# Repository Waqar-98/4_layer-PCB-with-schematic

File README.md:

4-Layer ESP32 Sensor Board

A battery-powered, USB-C rechargeable ESP32-C3 sensor node integrating environmental (temperature/humidity/pressure), ambient light, and sound sensing, with onboard USB-to-UART programming, microSD data logging, and an I2C display header. This repository is a **revision** of the original 2-layer design, re-laid-out as a **4-layer PCB** (dedicated inner power/ground planes) for improved signal integrity and routing.

| | |
|---|---|
| **MCU/Module** | ESP32-C3-WROOM-02-H4 (U3) |
| **USB-UART Bridge** | Silicon Labs CP2102N-A02-GQFN20 (U4) |
| **Layers** | 4 (F.Cu, In1.Cu, In2.Cu, B.Cu) |
| **Interfaces** | USB-C (USB 2.0), I2C, microSD (SPI), SPI NOR flash, GPIO breakout |
| **Power** | USB-C 5 V input, single-cell LiPo (JST 2 mm), onboard charge management |
| **Revision** | 2 (4-layer revision) |
| **Status** | In development |

---

## Table of Contents

1. [Overview](#1-overview)
2. [Features](#2-features)
3. [Hardware Description](#3-hardware-description)
4. [Schematics](#4-schematics)
5. [PCB Layout](#5-pcb-layout)
6. [ESP32-C3 Pin Mapping](#6-esp32-c3-pin-mapping)
7. [Connector Pinout](#7-connector-pinout)
8. [Power Supply](#8-power-supply)
9. [Getting Started](#9-getting-started)
10. [Repository Structure](#10-repository-structure)
11. [Bill of Materials](#11-bill-of-materials)
12. [Revision History](#12-revision-history)

---

## 1. Overview

This board is a compact, self-contained sensor node built around the ESP32-C3-WROOM-02-H4 module. It integrates a BME280 environmental sensor, a TEMT6000 ambient light sensor, and an electret microphone with an adjustable-gain amplifier, alongside a microSD card slot and an external SPI NOR flash for local data logging. Power comes from either USB-C or a single-cell LiPo battery, with onboard charge management and power-path switching so the board can run and charge simultaneously. An onboard CP2102N provides USB-to-UART programming and an automatic reset/bootloader-entry circuit, so no external programmer is required.

This revision re-lays out the board on **4 copper layers** instead of 2, adding dedicated inner power (3.3 V) and ground planes. This improves return-path continuity and reduces plane impedance/noise for the analog sensor front-ends (microphone amplifier, light sensor) and the SPI/I2C digital buses, compared with the original 2-layer version.

## 2. Features

- **ESP32-C3-WROOM-02-H4** (U3) — RISC-V single-core Wi-Fi/BLE module
- **BME280** (U7) environmental sensor — temperature, humidity, and pressure over I2C, address-select pad for 0x76/0x77
- **TEMT6000X01** (Q1) ambient light phototransistor with RC-filtered analog output
- **Electret microphone** (MK1, CMC-5042PF-AC) with a **MAX4466EXK+T** (U8) op-amp amplifier and a trimmer potentiometer (R17, 100 kΩ) for adjustable gain
- **microSD card slot** (J3, GSD090012SEU) on a shared SPI bus
- **32 Mbit external SPI NOR flash** (U6, W25Q32JVSSIQ) sharing the same SPI bus with an independent chip select, for onboard data logging separate from the module's program flash
- **Onboard USB-to-UART bridge** (U4, CP2102N-A02-GQFN20) with USB ESD protection (U5, USBLC6-2SC6) — no external FTDI/CH340 adapter needed to program the board
- **Automatic reset/bootloader-entry circuit** using two BC817 transistors (Q2, Q3) driven from DTR/RTS, following the standard ESP32 auto-program sequence
- **USB-C power input** (J1) with 5.1 kΩ CC pull-downs for default 5 V/USB 2.0 negotiation
- **LiPo charge management** via a **MCP73871** charger IC (U1) with power-path management, tri-color charge-status LEDs (charging/charged/power-good), and battery connector (J2, JST 2 mm)
- **LM1117MPX-3.3** LDO (U2) regulates the system 3.3 V rail
- Manual **BOOT** and **RESET** buttons (SW1, SW2) in addition to the automatic DTR/RTS circuit
- I2C header (J4) for an external OLED display
- 5-pin breakout header (J6) exposing 3.3 V, GND, and three spare GPIOs (GPIO8, GPIO18, GPIO19)
- Five test points (TP1–TP5) on the shared SPI bus (MOSI, MISO, SCLK, CS_SD, CS) for debugging
- **4-layer stack-up** with dedicated inner 3.3 V and GND planes (this revision)

## 3. Hardware Description

**Power input and charging.** USB-C VBUS (J1) passes through a resettable fuse (F1) to the `+5V_USB` rail. This rail feeds a MCP73871 LiPo charger IC (U1) configured with power-path management: it charges a single-cell LiPo connected at J2 while simultaneously supplying the system load from its `OUT` pin, so the board can operate while charging. Three status outputs (`STAT1`, `STAT2`, `PG`) drive a red/green/blue LED trio (D1–D3) through 470 Ω resistors, giving a visual charge/power-good indication. `OUT` feeds through a ferrite bead (FB1) into an LM1117MPX-3.3 LDO (U2), which produces the board's 3.3 V rail used by every other block.

**MCU and USB programming.** The ESP32-C3-WROOM-02-H4 (U3) is the central module. A CP2102N-A02-GQFN20 USB-to-UART bridge (U4), protected by a USBLC6-2SC6 ESD array (U5) on the USB data lines, connects the module's TX/RX to the host PC and exposes green/red (D5/D6) activity LEDs on its GPIO.2/GPIO.3 lines. DTR and RTS from the CP2102N drive two BC817 transistors (Q2, Q3) that implement the standard auto-reset/auto-bootloader circuit on the `EN` and `BOOT` (GPIO9) lines, so the board can be flashed without manually holding a button. Manual BOOT (SW1) and RESET (SW2) buttons are also provided, each with an RC debounce network.

Notably, because the ESP32-C3's boot-mode strapping pin is GPIO9 (unlike the original ESP32, which straps on GPIO0), this design routes GPIO9 to the `BOOT` net for auto-programming and frees GPIO0 for use as an analog input for the microphone signal (`MIC_OUT`).

**Storage.** A microSD socket (J3, GSD090012SEU) and a 32 Mbit SPI NOR flash (U6, W25Q32JVSSIQ) share one SPI bus (`MOSI_DI`, `MISO_DO`, `SCLK`) with independent chip-select lines (`CS_SD`, `CS`). Series resistors (R15, R20, R22 — annotated on the schematic as ~50 Ω) sit on the shared bus lines to damp ringing at high SPI clock rates. Five test points (TP1–TP5) break out the same bus for probing.

**Sensors.** A BME280 (U7) provides temperature, humidity, and pressure over I2C, with SDA/SCL pull-ups (R24, R25) and a pad to select the I2C address by tying `SDO` to GND (0x76) or `VDDIO` (0x77) — this board ties it to GND. A TEMT6000X01 phototransistor (Q1) with a 10 kΩ pull-down (R23) and RC filtering forms a simple ambient-light sensor read as an analog voltage. An electret microphone (MK1) is biased and AC-coupled into a MAX4466EXK+T op-amp (U8) configured as a non-inverting amplifier; a 22 kΩ resistor plus a 100 kΩ trimmer potentiometer (R31, R17) in the feedback path set the gain, with a 100 pF capacitor (C20) rolling off high-frequency noise.

**User interface.** A 4-pin I2C header (J4, B4B-XH-AM) breaks out 3.3 V/SDA/SCL/GND for an external OLED display. A 5-pin header (J6) exposes 3.3 V, GND, and the three GPIOs (GPIO8/18/19) not otherwise used by the design.

**Stack-up (this revision).** The board was re-laid-out from 2 to 4 copper layers: `F.Cu` (top signal), `In1.Cu` (inner plane), `In2.Cu` (inner plane), `B.Cu` (bottom signal). The inner layers are used as continuous 3.3 V and GND planes, giving the top/bottom signal layers a solid adjacent reference plane and shortening high-frequency return paths for the SPI bus and analog front-ends.

## 4. Schematics

**Power and battery management** (root sheet — USB-C input, LiPo charger, LDO regulator, power-indicator LED, battery connector)

**ESP32-C3-02 and USB-to-UART converter** (MCU, CP2102N USB bridge, SPI flash, microSD module, test points)

**Sensors** (BME280, TEMT6000 light sensor, electret microphone and amplifier)

**User interface** (OLED I2C header, GPIO breakout header, reset/boot buttons, auto-program circuit)

## 5. PCB Layout

Four-layer board (top copper in red, bottom copper in blue, inner planes not separately colored in the 2D view) with a stepped outline: the sensor cluster (microphone, light sensor, BME280) sits along the top edge, charging/regulation/USB circuitry occupies the left and lower-left, and the ESP32 module, SPI flash, and microSD slot are grouped on the right where the board extends further along the top edge. A hatched keep-out zone sits directly next to the ESP32-C3-WROOM-02 footprint, consistent with the module's onboard PCB antenna clearance requirement. A second hatched/unpopulated zone, silkscreened `proto#2`, appears to be a reserved prototyping area. The layout includes multiple mounting holes and five silkscreened test points (TP1–TP5) on the shared SPI bus — exact hole counts, diameters, and keep-out dimensions should be confirmed against the PCB source file.

**3D Render**

## 6. ESP32-C3 Pin Mapping

Pin assignments below are read directly from the ESP32-C3-WROOM-02-H4 (U3) schematic symbol. Verify against the source design files prior to firmware development.

| Module Pin | GPIO | Net / Function |
|---|---|---|
| 1 | 3V3 | 3.3 V supply |
| 2 | EN | Chip enable / reset (auto-program + RESET button) |
| 18 | IO0 | `MIC_OUT` — microphone amplifier analog output |
| 17 | IO1 | `PHOTO_C` — light sensor analog output |
| 16 | IO2 | `MISO_DO` — shared SPI bus (flash + microSD) |
| 15 | IO3 | `SCL` — I2C clock (BME280, OLED header) |
| 3 | IO4 | `SDA` — I2C data (BME280, OLED header) |
| 4 | IO5 | `CS_SD` — microSD chip select |
| 5 | IO6 | `SCLK` — shared SPI bus clock (via R20) |
| 6 | IO7 | `MOSI_DI` — shared SPI bus data out (via R15) |
| 7 | IO8 | `GPIO8` — broken out to J6 |
| 8 | IO9 | `BOOT` — boot-mode strap / auto-program (via Q3) |
| 10 | IO10 | `CS` — SPI flash chip select |
| 13 | IO18 | `GPIO18` — broken out to J6 |
| 14 | IO19 | `GPIO19` — broken out to J6 |
| 12 | TXD | `RX_TX` — to CP2102N |
| 11 | RXD | `TX_RX` — from CP2102N |
| — | GND | Ground |

## 7. Connector Pinout

Pin assignments below are derived from the schematics. Verify against the source design files and PCB silkscreen prior to integration.

**J1 — USB-C Receptacle (USB 2.0 only)**

Standard USB-C receptacle; only the VBUS, GND, D+/D− and CC1/CC2 pins are used (SBU1/SBU2 and the SuperSpeed pairs are unconnected). CC1 and CC2 each carry a 5.1 kΩ pull-down (R4, R3) to present the board as a default-power USB 2.0 sink.

**J2 — Battery Connector (JST_2mm_LiPo)**

| Pin | Signal |
|-----|--------|
| 1 | VBAT (+) |
| 2 | GND |

**J3 — microSD Socket (GSD090012SEU), SPI mode**

| Pin | Signal |
|-----|--------|
| 4 | VDD1 (3.3 V) |
| 2 | CMD ← `MOSI_DI` |
| 5 | CLK ← `SCLK` |
| 7 | DAT0 → `MISO_DO` (pull-up R16) |
| 8 | DAT1 (not used in SPI mode) |
| 9 | DAT2 |
| 1 | CD/DAT3 → `CS_SD` (pull-up R19, 10 kΩ) |
| — | CD_IND, WP (not populated) |
| 3, 6 | VSS1/VSS2 (GND) |
| GS | SHIELD_GND |

**J4 — OLED Display Connector, I2C (B4B-XH-AM, 4-pin)**

| Pin | Signal |
|-----|--------|
| 1 | 3.3 V |
| 2 | SDA |
| 3 | SCL |
| 4 | GND |

**J6 — Spare GPIO Breakout (Conn_01x05, 5-pin)**

| Pin | Signal |
|-----|--------|
| 1 | 3.3 V |
| 2 | GPIO8 |
| 3 | GPIO18 |
| 4 | GPIO19 |
| 5 | GND |

**TP1–TP5 — Test Points**

| Test Point | Net |
|---|---|
| TP1 | MOSI_DI |
| TP2 | MISO_DO |
| TP3 | SCLK |
| TP4 | CS_SD |
| TP5 | CS |

## 8. Power Supply

| Parameter | Value |
|---|---|
| Input | USB-C 5 V (VBUS, via resettable fuse F1) or single-cell LiPo (J2) |
| Charger IC | MCP73871 (U1) — LiPo charger with power-path management |
| Regulator | LM1117MPX-3.3/NDPB (U2), LDO |
| System rail | 3.3 V |
| Charge status indication | Tri-color LED (D1 red / D2 green / D3 blue) driven from STAT2, STAT1/LBO, PG |
| Power-good indicator | Red LED (D4) on the 3.3 V rail via R10 (330 Ω) |
| Input filtering | C1 (0.1 µF) on VBUS; C2/C3 (0.1 µF/10 µF) on LDO input; C4/C5 (10 µF/0.1 µF) on LDO output; C6 (1 µF) on charger IN |

## 9. Getting Started

1. **Power:** Connect a USB-C cable to J1 for bench power/programming, and/or connect a single-cell LiPo battery to J2 for portable operation. The board can run while charging.
2. **Programming:** Connect the board to a host PC via USB-C. The onboard CP2102N enumerates as a serial port; the DTR/RTS auto-program circuit puts the ESP32-C3 into bootloader mode automatically when flashing (e.g. via `esptool.py` or the Arduino/PlatformIO/ESP-IDF toolchains). Use the BOOT (SW1) and RESET (SW2) buttons manually if auto-programming is disabled or unresponsive.
3. **Serial/communication:** The BME280 and any OLED display connected at J4 share the I2C bus on GPIO3 (SCL) / GPIO4 (SDA). The microSD card and external SPI flash share one SPI bus (GPIO6/7/2) with independent chip selects on GPIO5 (`CS_SD`) and GPIO10 (`CS`).
4. **Opening the design:** Open `hardware/kicad/ESP32 sensor board.kicad_pro` in KiCad 8/9+ to view or edit the schematic and 4-layer PCB layout.
5. **Fabrication:** Fabrication-ready Gerbers and drill files for the current 4-layer revision are in `hardware/gerbers/`, generated directly from the KiCad PCB source.

## 10. Repository Structure

```
.
├── docs/
│   └── images/
│       ├── schematic-power-management.png
│       ├── schematic-mcu-usb-uart.png
│       ├── schematic-sensors.png
│       ├── schematic-user-interface.png
│       ├── pcb-layout.png
│       └── pcb-3d-render.png
├── hardware/
│   ├── kicad/            # Full KiCad 4-layer project source (schematics, PCB, libraries, datasheets)
│   ├── gerbers/           # Fabrication-ready Gerber and drill files (4-layer)
│   └── bom.csv            # Bill of materials, exported from the schematic
└── README.md
```

## 11. Bill of Materials

A full bill of materials, generated from the schematic, is available at [`hardware/bom.csv`](hardware/bom.csv). Key components:

| Reference | Component | Description |
|---|---|---|
| U1 | MCP73871 | LiPo charger IC with power-path management |
| U2 | LM1117MPX-3.3/NDPB | 3.3 V LDO regulator |
| U3 | ESP32-C3-WROOM-02-H4 | Wi-Fi/BLE MCU module |
| U4 | CP2102N-A02-GQFN20 | USB-to-UART bridge |
| U5 | USBLC6-2SC6 | USB D+/D− ESD protection array |
| U6 | W25Q32JVSSIQ | 32 Mbit SPI NOR flash |
| U7 | BME280 | Environmental sensor (temperature/humidity/pressure) |
| U8 | MAX4466EXK+T | Microphone amplifier op-amp |
| Q1 | TEMT6000X01 | Ambient light phototransistor |
| Q2, Q3 | BC817 | NPN transistors, auto-reset/bootloader circuit |
| MK1 | CMC-5042PF-AC | Electret microphone |
| J1 | USB_C_Receptacle | USB-C connector |
| J2 | JST_2mm_LiPo | Battery connector |
| J3 | GSD090012SEU | microSD card socket |
| J4 | B4B-XH-AM | 4-pin JST-XH, OLED I2C connector |
| J6 | Conn_01x05 | 5-pin GPIO breakout header |
| SW1, SW2 | Tactile switch | BOOT and RESET buttons |
| D1–D3 | LED (RGB, discrete) | Charge status indicator |
| D4 | LED (red) | Power-good indicator |
| D5, D6 | LED (green/red) | USB activity indicators |
| F1 | Resettable fuse | VBUS overcurrent protection |
| FB1 | Ferrite bead | Charger output filtering |

## 12. Revision History

| Revision | Date | Notes |
|---|---|---|
| 1 | 2026-06-29 | Initial 2-layer design |
| 2 | 2026-09-09 | Revised to 4-layer stack-up with dedicated inner power/ground planes; gerbers and BOM regenerated for the new layout |

---

**Author:** Waqar-98

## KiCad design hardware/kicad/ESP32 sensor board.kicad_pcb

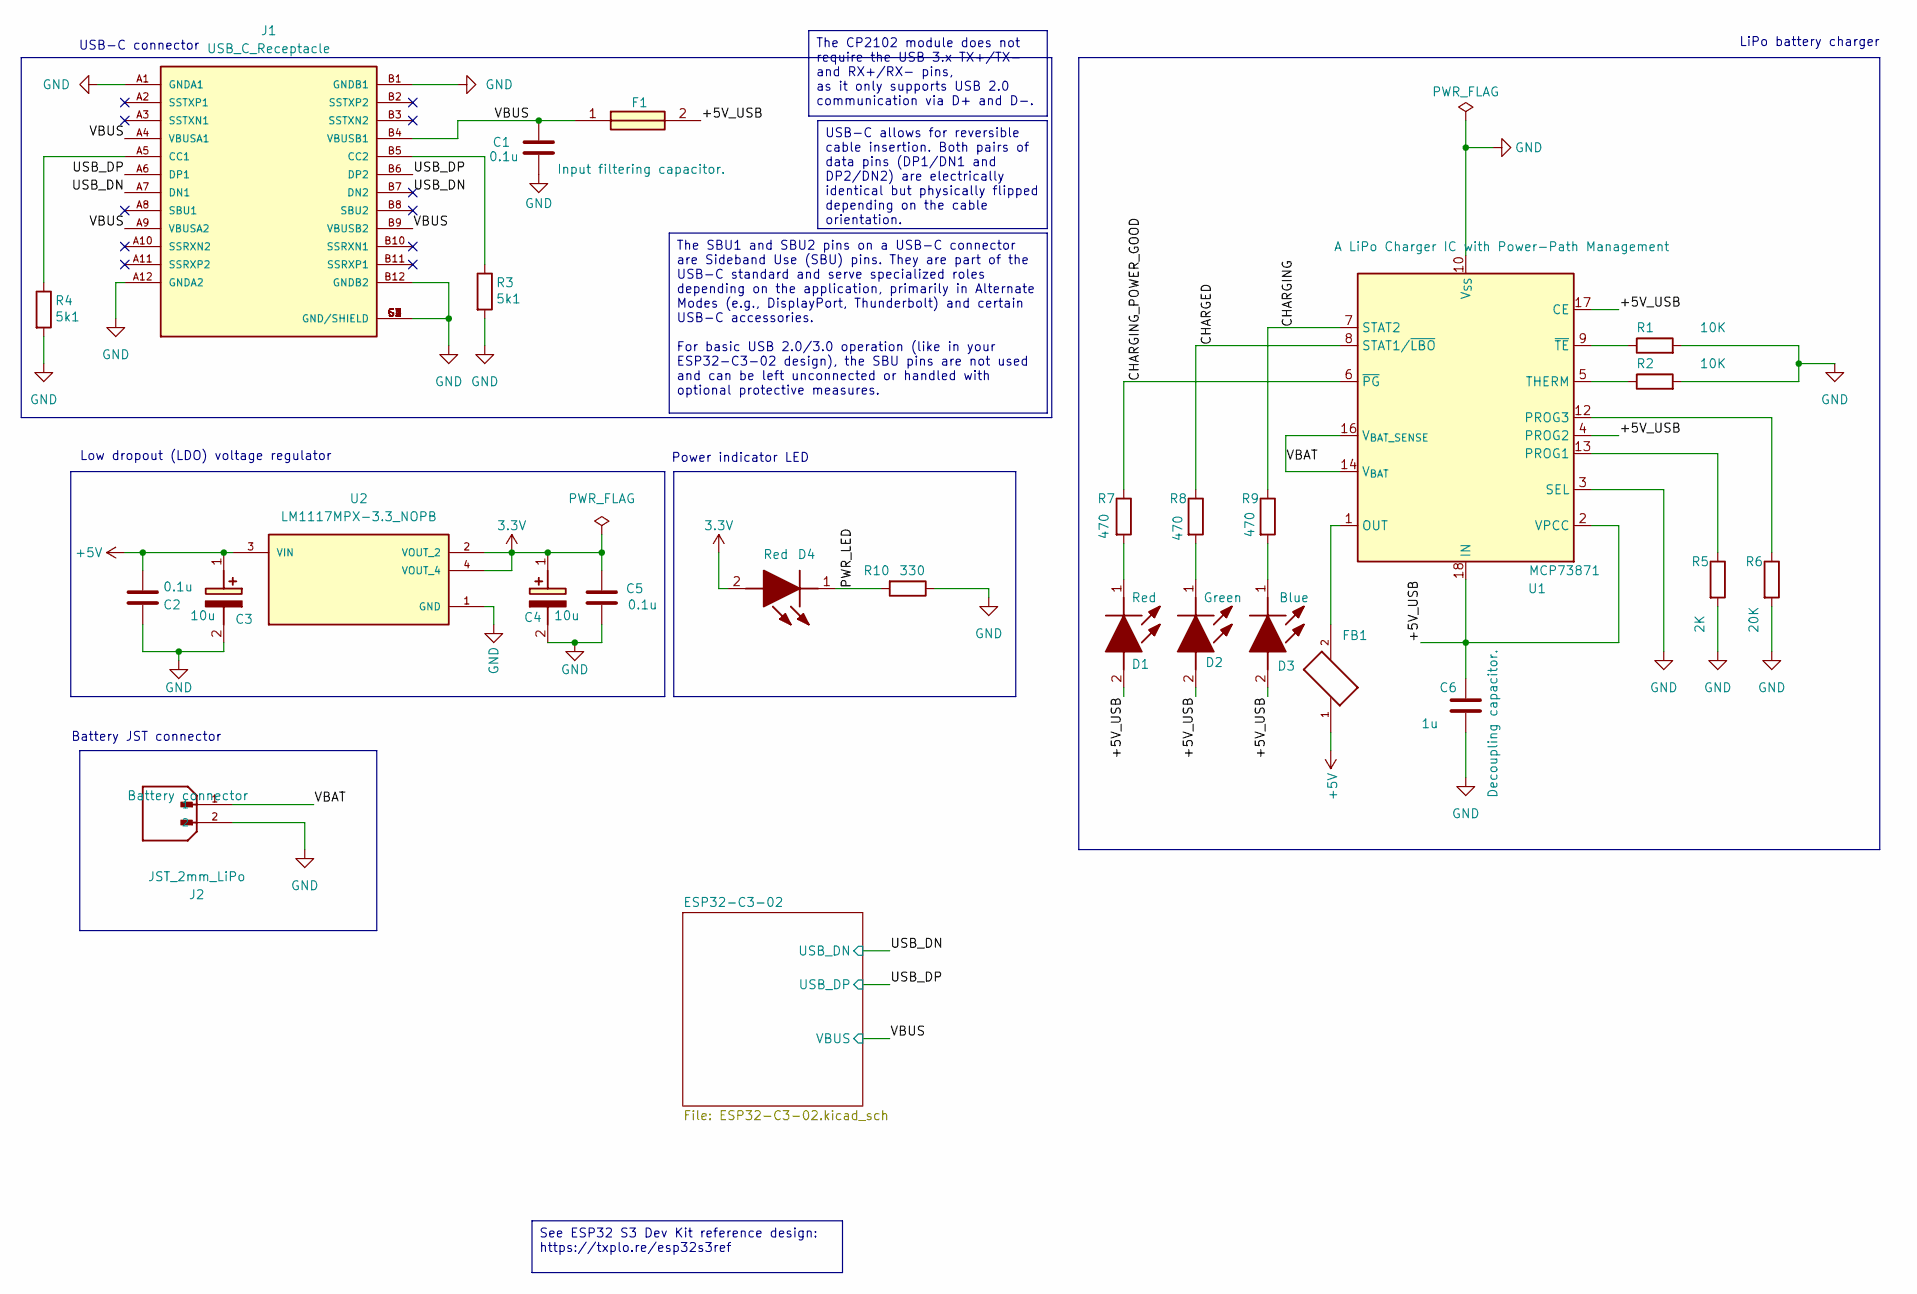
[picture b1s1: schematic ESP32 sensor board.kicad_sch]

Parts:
C1, C2, C5: 0.1u; C_0805_2012Metric; Voltage 1kV; Tolerance 100%
C3, C4: 10u; T491A; Voltage 1kV; Tolerance 100%; Manufacturer_Part_Number T491A106K010AT7280; Mouser Part Number 80-T491A106K107280
C6: 1u; C_0805_2012Metric; Voltage 1kV; Tolerance 100%
D1, D4: Red; LEDC2012X120N; Manufacturer_Part_Number LTST-C170KRKT; Mouser Part Number 859-LTST-C170KRKT
D2: Green; LEDC2012X120N; Manufacturer_Part_Number LTST-C170GKT; Mouser Part Number 859-LTST-C170GKT
D3: Blue; LEDC2012X120N; Manufacturer_Part_Number LTST-C170TBKT; Mouser Part Number 859-LTST-C170TBKT
F1: 0ZCH0110AF2E; FUSC3226X100N; Manufacturer_Part_Number 0ZCH0110AF2E
FB1: FBMJ2125HM330-T; BEADC2012X105N
J1: USB_C_Receptacle; BELFUSE_SS-52400-002; PARTREV A0
J2: JST_2mm_LiPo; JST_B2B-PH-SM4-TB; Manufacturer_Part_Number ?
R1, R2: 10K; R_0805_2012Metric
R3, R4: 5k1; R_0805_2012Metric
R5: 2K; R_0805_2012Metric
R6: 20K; R_0805_2012Metric
R7, R8, R9: 470; R_0805_2012Metric
R10: 330; R_0805_2012Metric
U1: MCP73871; QFN-20-1EP_4x4mm_P0.5mm_EP2.5x2.5mm; Manufacturer_Part_Number MCP73871-4CCI/ML
U2: LM1117MPX-3.3_NOPB; VREG_LM1117MPX-3.3; Mouser Part Number 926-LM1117MPX3.3NOPB

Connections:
3.3V: C4.1 (+), C5.1, D4.2 (A), U2.2 (VOUT_2), U2.4 (VOUT_4); also elsewhere on the board
+5V: C2.1, C3.1 (+), FB1.1, U2.3 (VIN)
/+5V_USB: C6.1, D1.2 (A), D2.2 (A), D3.2 (A), F1.2, U1.2 (VPCC), U1.4 (PROG2), U1.17 (CE), U1.18 (IN), U1.19 (IN)
/CHARGED: R8.1, U1.8 (STAT1/~LBO)
/CHARGING: R9.1, U1.7 (STAT2)
/CHARGING_POWER_GOOD: R7.1, U1.6 (~PG)
/PWR_LED: D4.1 (K), R10.2
/USB_DN: J1.A7 (DN1), J1.B7 (DN2); also elsewhere on the board
/USB_DP: J1.A6 (DP1), J1.B6 (DP2); also elsewhere on the board
/VBAT: J2.1, U1.14 (V_{BAT}), U1.15 (V_{BAT}), U1.16 (V_{BAT_SENSE})
/VBUS: C1.1, F1.1, J1.A4 (VBUSA1), J1.A9 (VBUSA2), J1.B4 (VBUSB1), J1.B9 (VBUSB2); also elsewhere on the board
unnamed: D1.1 (K), R7.2
unnamed: D2.1 (K), R8.2
unnamed: D3.1 (K), R9.2
unnamed: FB1.2, U1.1 (OUT), U1.20 (OUT)
unnamed: J1.A5 (CC1), R4.1
unnamed: J1.B5 (CC2), R3.1
unnamed: R5.1, U1.13 (PROG1)
unnamed: R6.1, U1.12 (PROG3)
unnamed: R2.1, U1.5 (THERM)
unnamed: R1.1, U1.9 (~TE)

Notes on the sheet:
USB-C connector
LiPo battery charger
Power indicator LED
Low dropout (LDO) voltage regulator
Battery JST connector
The CP2102 module does not require the USB 3.x TX+/TX- and RX+/RX- pins, as it only supports USB 2.0 communication via D+ and D-.
See ESP32 S3 Dev Kit reference design: https://txplo.re/esp32s3ref
The SBU1 and SBU2 pins on a USB-C connector are Sideband Use (SBU) pins. They are part of the USB-C standard and serve specialized roles depending on the application, primarily in Alternate Modes (e.g., DisplayPort, Thunderbolt) and certain USB-C accessories. For basic USB 2.0/3.0 operation (like i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
USB-C allows for reversible cable insertion. Both pairs of data pins (DP1/DN1 and DP2/DN2) are electrically identical but physically flipped depending on the cable orientation.

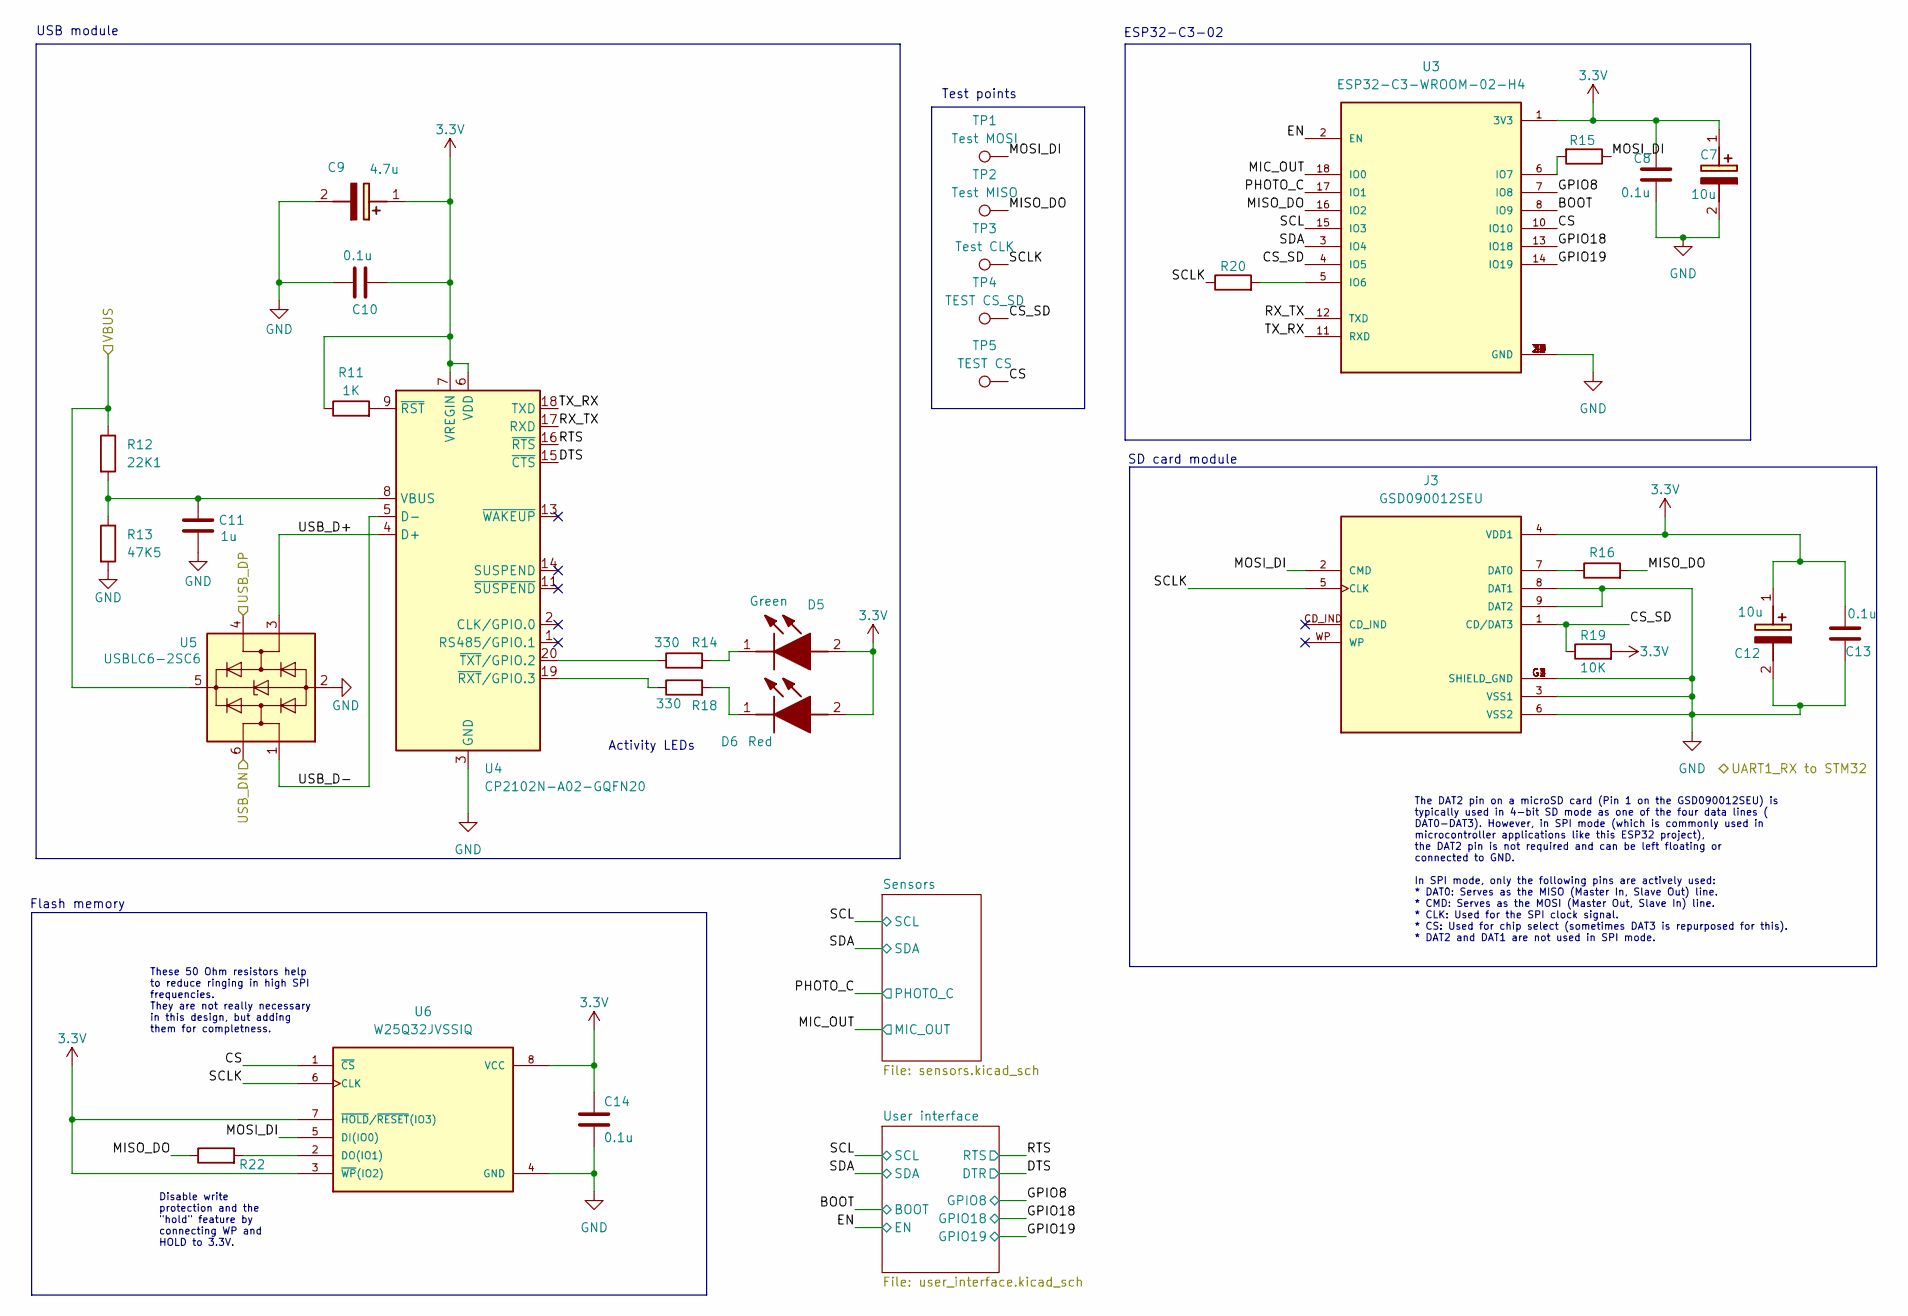
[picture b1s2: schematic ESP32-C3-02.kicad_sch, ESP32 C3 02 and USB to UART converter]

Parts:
C7, C12: 10u; T491A; Voltage 1kV; Tolerance 100%; Manufacturer_Part_Number T491A106K010AT7280; Mouser Part Number 80-T491A106K107280
C8, C10, C13, C14: 0.1u; C_0805_2012Metric; Voltage 1kV; Tolerance 100%
C9: 4.7u; T491A; Voltage 1kV; Tolerance 100%; Manufacturer_Part_Number T491A106K010AT7280; Mouser Part Number 80-T491A106K107280
C11: 1u; C_0805_2012Metric; Voltage 1kV; Tolerance 100%
D5: Green; LEDC2012X120N; Manufacturer_Part_Number LTST-C170GKT; Mouser Part Number 859-LTST-C170GKT
D6: Red; LEDC2012X120N; Manufacturer_Part_Number LTST-C170KRKT; Mouser Part Number 859-LTST-C170KRKT
J3: GSD090012SEU; AMPHENOL_GSD090012SEU; PARTREV E
R11: 1K; R_0805_2012Metric
R12: 22K1; R_0805_2012Metric
R13: 47K5; R_0805_2012Metric
R14, R18: 330; R_0805_2012Metric
R15, R16, R20, R22: 50; R_0805_2012Metric
R19: 10K; R_0805_2012Metric
TP1: Test MOSI; TestPoint_Pad_D1.0mm
TP2: Test MISO; TestPoint_Pad_D1.0mm
TP3: Test CLK; TestPoint_Pad_D1.0mm
TP4: TEST CS_SD; TestPoint_Pad_D1.0mm
TP5: TEST CS; TestPoint_Pad_D1.0mm
U3: ESP32-C3-WROOM-02-H4; MODULE_ESP32-C3-WROOM-02-H4; Manufacturer_Part_Number ESP32-C3-WROOM-02-H4
U4: CP2102N-A02-GQFN20; SiliconLabs_QFN-20-1EP_3x3mm_P0.5mm_EP1.8x1.8mm; Manufacturer_Part_Number CP2102N-A02-GQFN20
U5: USBLC6-2SC6; SOT-23-6; Manufacturer_Part_Number USBLC6-2SC6; Mouser Part Number 511-USBLC6-2SC6
U6: W25Q32JVSSIQ; SOIC127P790X216-8N; M_PART_NUMBER W25QXX

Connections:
3.3V: C7.1 (+), C8.1, C9.1 (+), C10.1, C12.1 (+), C13.2, C14.1, D5.2 (A), D6.2 (A), J3.4 (VDD1), R11.1, R19.2, U3.1 (3V3), U4.6 (VDD), U4.7 (VREGIN), U6.3 (~WP(IO2)), U6.7 (~HOLD/~RESET(IO3)), U6.8 (VCC); also elsewhere on the board
/ESP32-C3-02/CS: TP5.1, U3.10 (IO10), U6.1 (~CS)
/ESP32-C3-02/CS_SD: J3.1 (CD/DAT3), R19.1, TP4.1, U3.4 (IO5)
/ESP32-C3-02/DTS: U4.15 (~CTS); also elsewhere on the board
/ESP32-C3-02/GPIO8: U3.7 (IO8); also elsewhere on the board
/ESP32-C3-02/GPIO18: U3.13 (IO18); also elsewhere on the board
/ESP32-C3-02/GPIO19: U3.14 (IO19); also elsewhere on the board
/ESP32-C3-02/MIC_OUT: U3.18 (IO0); also elsewhere on the board
/ESP32-C3-02/MISO_DO: R16.2, R22.1, TP2.1, U3.16 (IO2)
/ESP32-C3-02/MOSI_DI: J3.2 (CMD), R15.1, TP1.1, U6.5 (DI(IO0))
/ESP32-C3-02/PHOTO_C: U3.17 (IO1); also elsewhere on the board
/ESP32-C3-02/RTS: U4.16 (~RTS); also elsewhere on the board
/ESP32-C3-02/RX_TX: U3.12 (TXD), U4.17 (RXD)
/ESP32-C3-02/SCL: U3.15 (IO3); also elsewhere on the board
/ESP32-C3-02/SCLK: J3.5 (CLK), R20.1, TP3.1, U6.6 (CLK)
/ESP32-C3-02/SDA: U3.3 (IO4); also elsewhere on the board
/ESP32-C3-02/TX_RX: U3.11 (RXD), U4.18 (TXD)
/ESP32-C3-02/USB_D+: U4.4 (D+), U5.3 (I/O2)
/ESP32-C3-02/USB_D-: U4.5 (D-), U5.1 (I/O1)
/USB_DN: U5.6 (I/O1); also elsewhere on the board
/USB_DP: U5.4 (I/O2); also elsewhere on the board
/VBUS: R12.1, U5.5 (VBUS); also elsewhere on the board
unnamed: D5.1 (K), R14.2
unnamed: D6.1 (K), R18.2
unnamed: J3.7 (DAT0), R16.1
unnamed: R20.2, U3.5 (IO6)
unnamed: R15.2, U3.6 (IO7)
unnamed: C11.1, R12.2, R13.1, U4.8 (VBUS)
unnamed: R11.2, U4.9 (~RST)
unnamed: R18.1, U4.19 (~RXT/GPIO.3)
unnamed: R14.1, U4.20 (~TXT/GPIO.2)
unnamed: R22.2, U6.2 (DO(IO1))

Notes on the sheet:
SD card module
Activity LEDs
Flash memory
USB module
Test points
ESP32-C3-02
Disable write protection and the "hold" feature by connecting WP and HOLD to 3.3V.
The DAT2 pin on a microSD card (Pin 1 on the GSD090012SEU) is typically used in 4-bit SD mode as one of the four data lines ( DAT0-DAT3). However, in SPI mode (which is commonly used in microcontroller applications like this ESP32 project), the DAT2 pin is not required and can be left floating or c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
These 50 Ohm resistors help to reduce ringing in high SPI frequencies. They are not really necessary in this design, but adding them for completness.

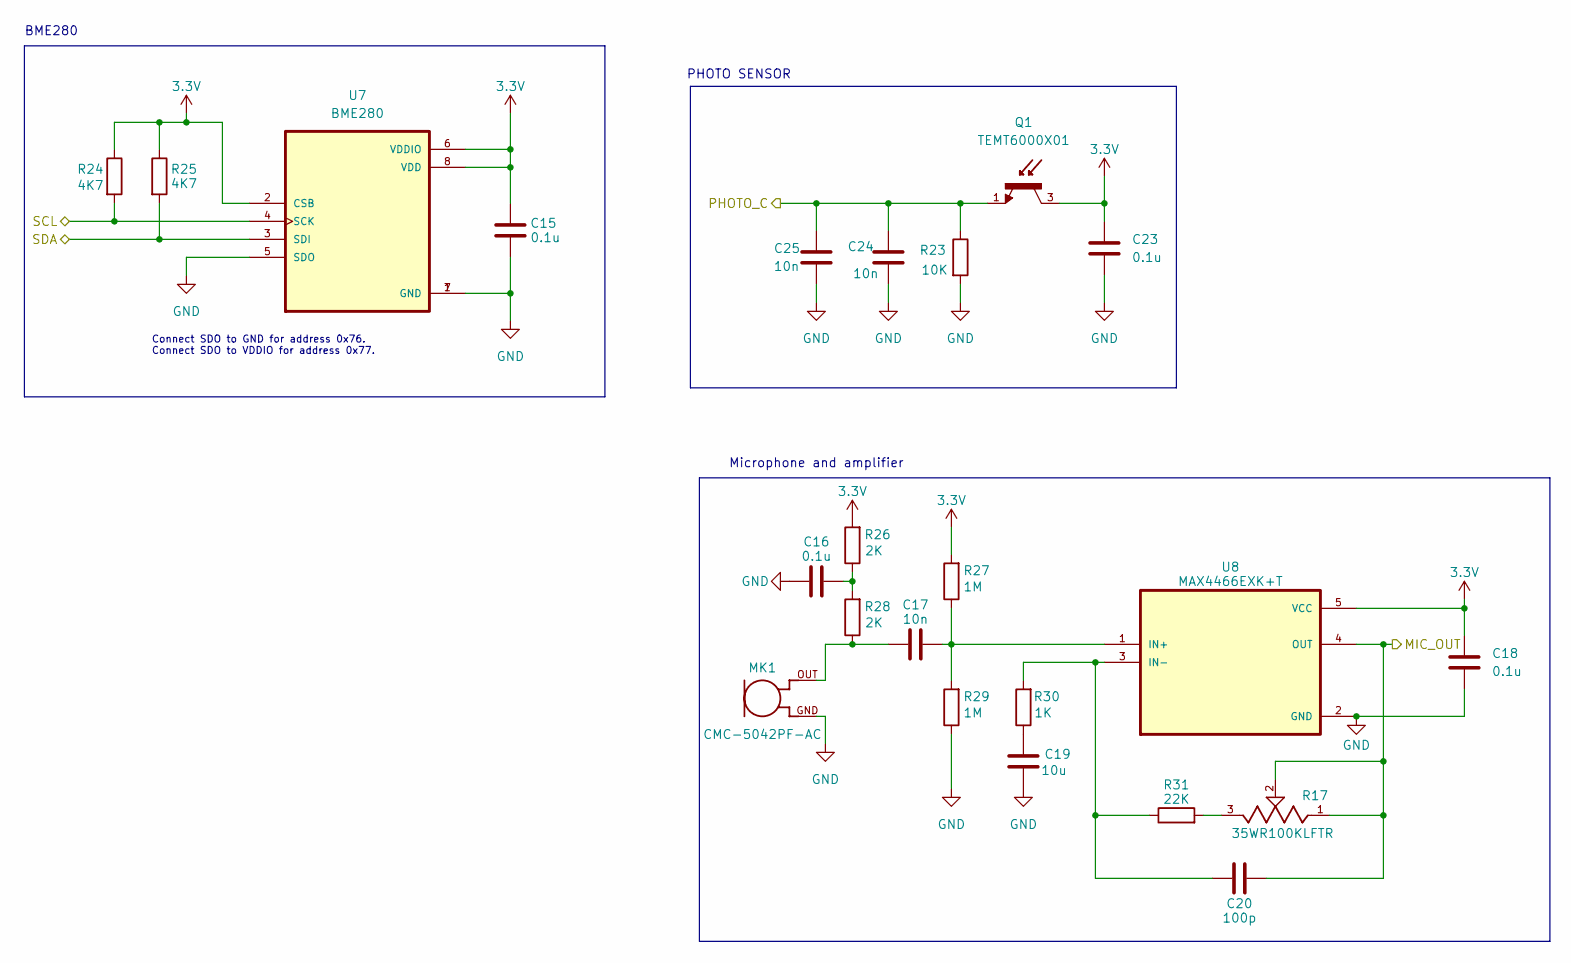
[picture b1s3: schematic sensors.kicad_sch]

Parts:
C15: 0.1u; C_0805_2012Metric; Voltage 1kV; Tolerance 100%
C16, C18, C23: 0.1u; C_0805_2012Metric
C17, C24, C25: 10n; C_0805_2012Metric
C19: 10u; C_0805_2012Metric
C20: 100p; C_0805_2012Metric
MK1: CMC-5042PF-AC; CUI_CMC-5042PF-AC; Manufacturer_Part_Number CMC-5042PF-AC
Q1: TEMT6000X01; TRANS_TEMT6000X01; PARTREV 1.9
R17: 35WR100KLFTR; TRIM_35WR100KLFTR; PARTREV D
R23: 10K; R_0805_2012Metric
R24, R25: 4K7; R_0805_2012Metric
R26, R28: 2K; R_0805_2012Metric
R27, R29: 1M; R_0805_2012Metric
R30: 1K; R_0805_2012Metric
R31: 22K; R_0805_2012Metric
U7: BME280; PSON65P250X250X100-8N; Manufacturer_Part_Number BME280
U8: MAX4466EXK+T; SOT65P210X110-5N; Manufacturer_Part_Number MAX4466EXK+T

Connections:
3.3V: C15.2, C18.1, C23.1, Q1.3, R24.1, R25.1, R26.2, R27.2, U7.2 (CSB), U7.6 (VDDIO), U7.8 (VDD), U8.5 (VCC); also elsewhere on the board
/ESP32-C3-02/MIC_OUT: C20.2, R17.1, R17.2, U8.4 (OUT); also elsewhere on the board
/ESP32-C3-02/PHOTO_C: C24.1, C25.1, Q1.1, R23.1; also elsewhere on the board
/ESP32-C3-02/SCL: R24.2, U7.4 (SCK); also elsewhere on the board
/ESP32-C3-02/SDA: R25.2, U7.3 (SDI); also elsewhere on the board
unnamed: C16.1, R26.1, R28.2
unnamed: C17.2, MK1.OUT, R28.1
unnamed: C19.2, R30.1
unnamed: R17.3, R31.2
unnamed: C17.1, R27.1, R29.2, U8.1 (IN+)
unnamed: C20.1, R30.2, R31.1, U8.3 (IN-)

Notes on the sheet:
PHOTO SENSOR
Microphone and amplifier
BME280
Connect SDO to GND for address 0x76. Connect SDO to VDDIO for address 0x77.

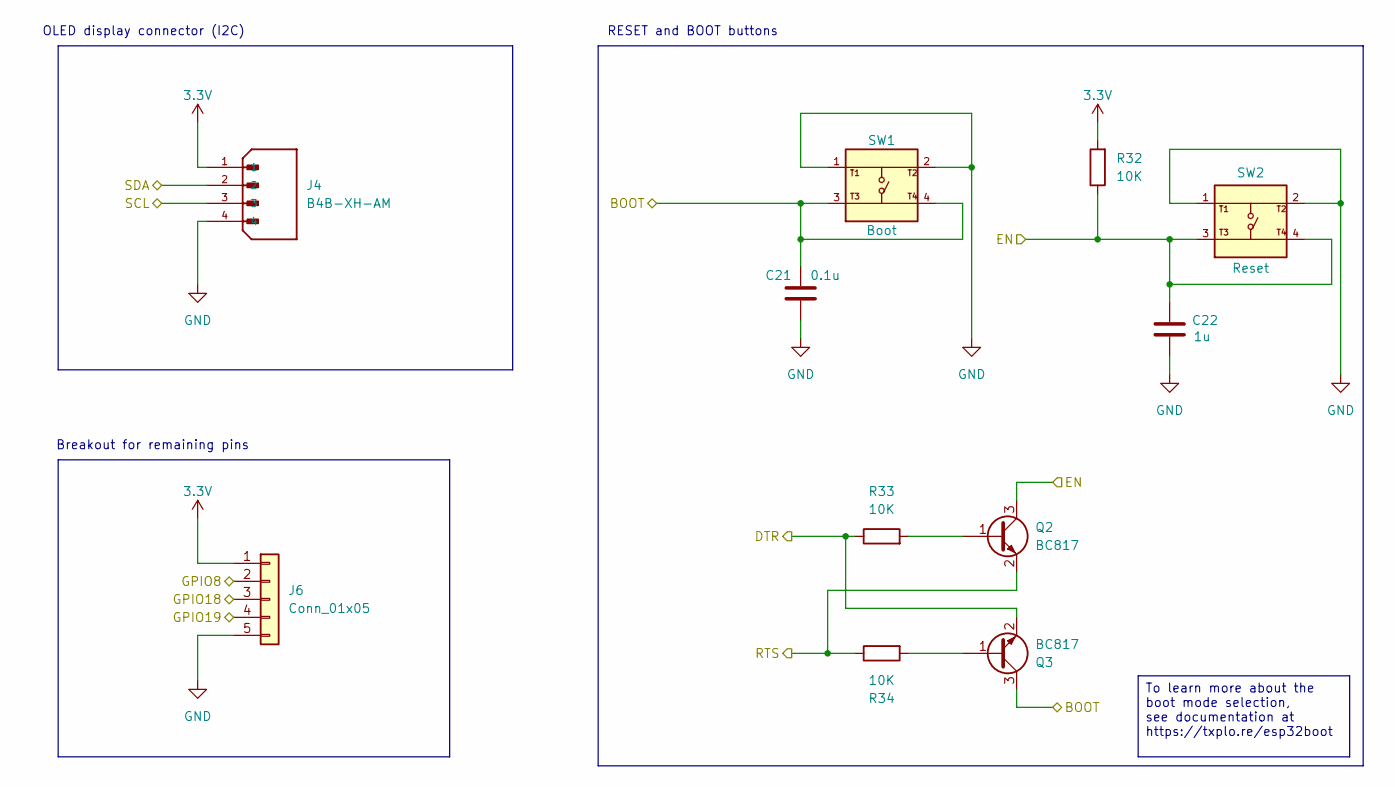
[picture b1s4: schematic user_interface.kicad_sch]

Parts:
C21: 0.1u; C_0805_2012Metric; Voltage 1kV; Tolerance 100%
C22: 1u; C_0805_2012Metric; Voltage 1kV; Tolerance 100%
J4: B4B-XH-AM; JST_B4B-XH-AM__LF__SN_; PARTREV N/A
J6: Conn_01x05; PinHeader_1x05_P2.54mm_Vertical
Q2, Q3: BC817; SOT-23; Manufacturer_Part_Number BC817
R32, R33, R34: 10K; R_0805_2012Metric
SW1, SW2: 1101NE; SW_USLPT2819DT2TR; Mfg Part# 8-004 SMD Button 8x3.6mm Height=2.5mm

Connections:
3.3V: J4.1, J6.1, R32.2; also elsewhere on the board
/ESP32-C3-02/DTS: Q3.2 (E), R33.1; also elsewhere on the board
/ESP32-C3-02/GPIO8: J6.2; also elsewhere on the board
/ESP32-C3-02/GPIO18: J6.3; also elsewhere on the board
/ESP32-C3-02/GPIO19: J6.4; also elsewhere on the board
/ESP32-C3-02/RTS: Q2.2 (E), R34.1; also elsewhere on the board
/ESP32-C3-02/SCL: J4.3; also elsewhere on the board
/ESP32-C3-02/SDA: J4.2; also elsewhere on the board
unnamed: Q2.1 (B), R33.2
unnamed: Q3.1 (B), R34.2

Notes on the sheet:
OLED display connector (I2C)
RESET and BOOT buttons
Breakout for remaining pins
To learn more about the boot mode selection, see documentation at https://txplo.re/esp32boot

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
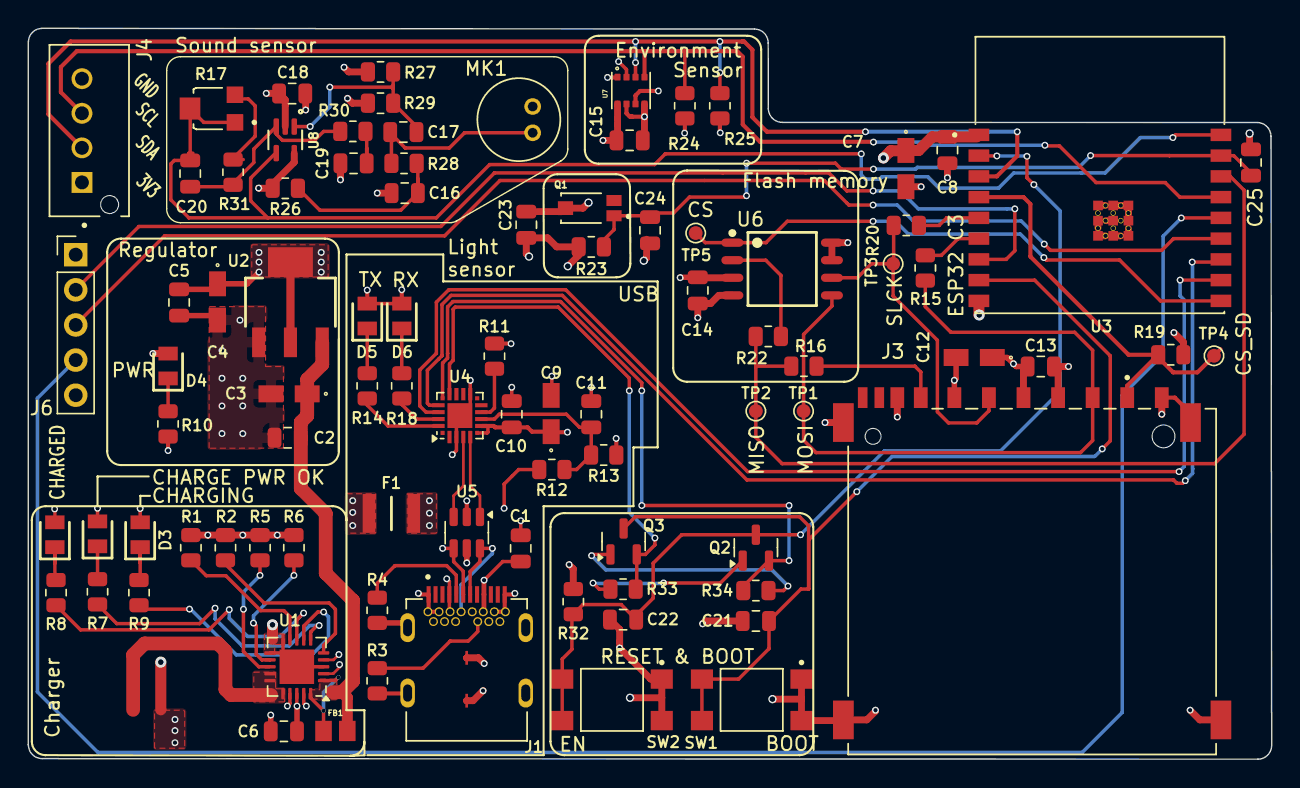
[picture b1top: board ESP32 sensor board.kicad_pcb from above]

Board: 4 copper layers, 89.9 x 52.8 mm, 89 parts (0 on the bottom side), 60 nets.

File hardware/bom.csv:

"Refs","Value","Footprint","Qty","DNP"
"C1","0.1u","Capacitor_SMD:C_0805_2012Metric","1",""
"C2","0.1u","Capacitor_SMD:C_0805_2012Metric","1",""
"C3","10u","Footprints:T491A","1",""
"C4","10u","Footprints:T491A","1",""
"C5","0.1u","Capacitor_SMD:C_0805_2012Metric","1",""
"C6","1u","Capacitor_SMD:C_0805_2012Metric","1",""
"C7","10u","Footprints:T491A","1",""
"C8","0.1u","Capacitor_SMD:C_0805_2012Metric","1",""
"C9","4.7u","Footprints:T491A","1",""
"C10","0.1u","Capacitor_SMD:C_0805_2012Metric","1",""
"C11","1u","Capacitor_SMD:C_0805_2012Metric","1",""
"C12","10u","Footprints:T491A","1",""
"C13","0.1u","Capacitor_SMD:C_0805_2012Metric","1",""
"C14","0.1u","Capacitor_SMD:C_0805_2012Metric","1",""
"C15","0.1u","Capacitor_SMD:C_0805_2012Metric","1",""
"C16","0.1u","Capacitor_SMD:C_0805_2012Metric","1",""
"C17","10n","Capacitor_SMD:C_0805_2012Metric","1",""
"C18","0.1u","Capacitor_SMD:C_0805_2012Metric","1",""
"C19","10u","Capacitor_SMD:C_0805_2012Metric","1",""
"C20","100p","Capacitor_SMD:C_0805_2012Metric","1",""
"C21","0.1u","Capacitor_SMD:C_0805_2012Metric","1",""
"C22","1u","Capacitor_SMD:C_0805_2012Metric","1",""
"C23","0.1u","Capacitor_SMD:C_0805_2012Metric","1",""
"C24","10n","Capacitor_SMD:C_0805_2012Metric","1",""
"C25","10n","Capacitor_SMD:C_0805_2012Metric","1",""
"D1","Red","Footprints:LEDC2012X120N","1",""
"D2","Green","Footprints:LEDC2012X120N","1",""
"D3","Blue","Footprints:LEDC2012X120N","1",""
"D4","Red","Footprints:LEDC2012X120N","1",""
"D5","Green","Footprints:LEDC2012X120N","1",""
"D6","Red","Footprints:LEDC2012X120N","1",""
"F1","0ZCH0110AF2E","Footprints:FUSC3226X100N","1",""
"FB1","FBMJ2125HM330-T","Footprints:BEADC2012X105N","1",""
"J1","USB_C_Receptacle","Footprints:BELFUSE_SS-52400-002","1",""
"J2","JST_2mm_LiPo","Footprints:JST_B2B-PH-SM4-TB","1",""
"J3","GSD090012SEU","Footprints:AMPHENOL_GSD090012SEU","1",""
"J4","B4B-XH-AM","Footprints:JST_B4B-XH-AM__LF__SN_","1",""
"J6","Conn_01x05","Connector_PinHeader_2.54mm:PinHeader_1x05_P2.54mm_Vertical","1",""
"MK1","CMC-5042PF-AC","Footprints:CUI_CMC-5042PF-AC","1",""
"Q1","TEMT6000X01","Footprints:TRANS_TEMT6000X01","1",""
"Q2","BC817","Package_TO_SOT_SMD:SOT-23","1",""
"Q3","BC817","Package_TO_SOT_SMD:SOT-23","1",""
"R1","10K","Resistor_SMD:R_0805_2012Metric","1",""
"R2","10K","Resistor_SMD:R_0805_2012Metric","1",""
"R3","5k1","Resistor_SMD:R_0805_2012Metric","1",""
"R4","5k1","Resistor_SMD:R_0805_2012Metric","1",""
"R5","2K","Resistor_SMD:R_0805_2012Metric","1",""
"R6","20K","Resistor_SMD:R_0805_2012Metric","1",""
"R7","470","Resistor_SMD:R_0805_2012Metric","1",""
"R8","470","Resistor_SMD:R_0805_2012Metric","1",""
"R9","470","Resistor_SMD:R_0805_2012Metric","1",""
"R10","330","Resistor_SMD:R_0805_2012Metric","1",""
"R11","1K","Resistor_SMD:R_0805_2012Metric","1",""
"R12","22K1","Resistor_SMD:R_0805_2012Metric","1",""
"R13","47K5","Resistor_SMD:R_0805_2012Metric","1",""
"R14","330","Resistor_SMD:R_0805_2012Metric","1",""
"R15","50","Resistor_SMD:R_0805_2012Metric","1",""
"R16","50","Resistor_SMD:R_0805_2012Metric","1",""
"R17","35WR100KLFTR","Footprints:TRIM_35WR100KLFTR","1",""
"R18","330","Resistor_SMD:R_0805_2012Metric","1",""
"R19","10K","Resistor_SMD:R_0805_2012Metric","1",""
"R20","50","Resistor_SMD:R_0805_2012Metric","1",""
"R22","50","Resistor_SMD:R_0805_2012Metric","1",""
"R23","10K","Resistor_SMD:R_0805_2012Metric","1",""
"R24","4K7","Resistor_SMD:R_0805_2012Metric","1",""
"R25","4K7","Resistor_SMD:R_0805_2012Metric","1",""
"R26","2K","Resistor_SMD:R_0805_2012Metric","1",""
"R27","1M","Resistor_SMD:R_0805_2012Metric","1",""
"R28","2K","Resistor_SMD:R_0805_2012Metric","1",""
"R29","1M","Resistor_SMD:R_0805_2012Metric","1",""
"R30","1K","Resistor_SMD:R_0805_2012Metric","1",""
"R31","22K","Resistor_SMD:R_0805_2012Metric","1",""
"R32","10K","Resistor_SMD:R_0805_2012Metric","1",""
"R33","10K","Resistor_SMD:R_0805_2012Metric","1",""
"R34","10K","Resistor_SMD:R_0805_2012Metric","1",""
"SW1","1101NE","USLPT2819DT2TR:SW_USLPT2819DT2TR","1",""
"SW2","1101NE","USLPT2819DT2TR:SW_USLPT2819DT2TR","1",""
"TP1","Test MOSI","TestPoint:TestPoint_Pad_D1.0mm","1",""
"TP2","Test MISO","TestPoint:TestPoint_Pad_D1.0mm","1",""
"TP3","Test CLK","TestPoint:TestPoint_Pad_D1.0mm","1",""
"TP4","TEST CS_SD","TestPoint:TestPoint_Pad_D1.0mm","1",""
"TP5","TEST CS","TestPoint:TestPoint_Pad_D1.0mm","1",""
"U1","MCP73871","Package_DFN_QFN:QFN-20-1EP_4x4mm_P0.5mm_EP2.5x2.5mm","1",""
"U2","LM1117MPX-3.3_NOPB","Footprints:VREG_LM1117MPX-3.3","1",""
"U3","ESP32-C3-WROOM-02-H4","Footprints:MODULE_ESP32-C3-WROOM-02-H4","1",""
"U4","CP2102N-A02-GQFN20","Package_DFN_QFN:SiliconLabs_QFN-20-1EP_3x3mm_P0.5mm_EP1.8x1.8mm","1",""
"U5","USBLC6-2SC6","Package_TO_SOT_SMD:SOT-23-6","1",""
"U6","W25Q32JVSSIQ","Footprints:SOIC127P790X216-8N","1",""
"U7","BME280","Footprints:PSON65P250X250X100-8N","1",""
"U8","MAX4466EXK+T","Footprints:SOT65P210X110-5N","1",""
